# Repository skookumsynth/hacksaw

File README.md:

# hacksaw

The core to an expandable VCO. Based on the ubiquitous integrator-reset design seen a billion times.

Planned expanders:

* Variable sync
* Waveshaper (Ramp, Double ramp, Triangle, Sine, Pulse, "Even" (as seen on the Befaco Even and Bergfotron).
* Suboctave generator w/ -1 and -2 Saw waves
* "Supersaw" stack
* Some manner of wavefolder
* AM and FM

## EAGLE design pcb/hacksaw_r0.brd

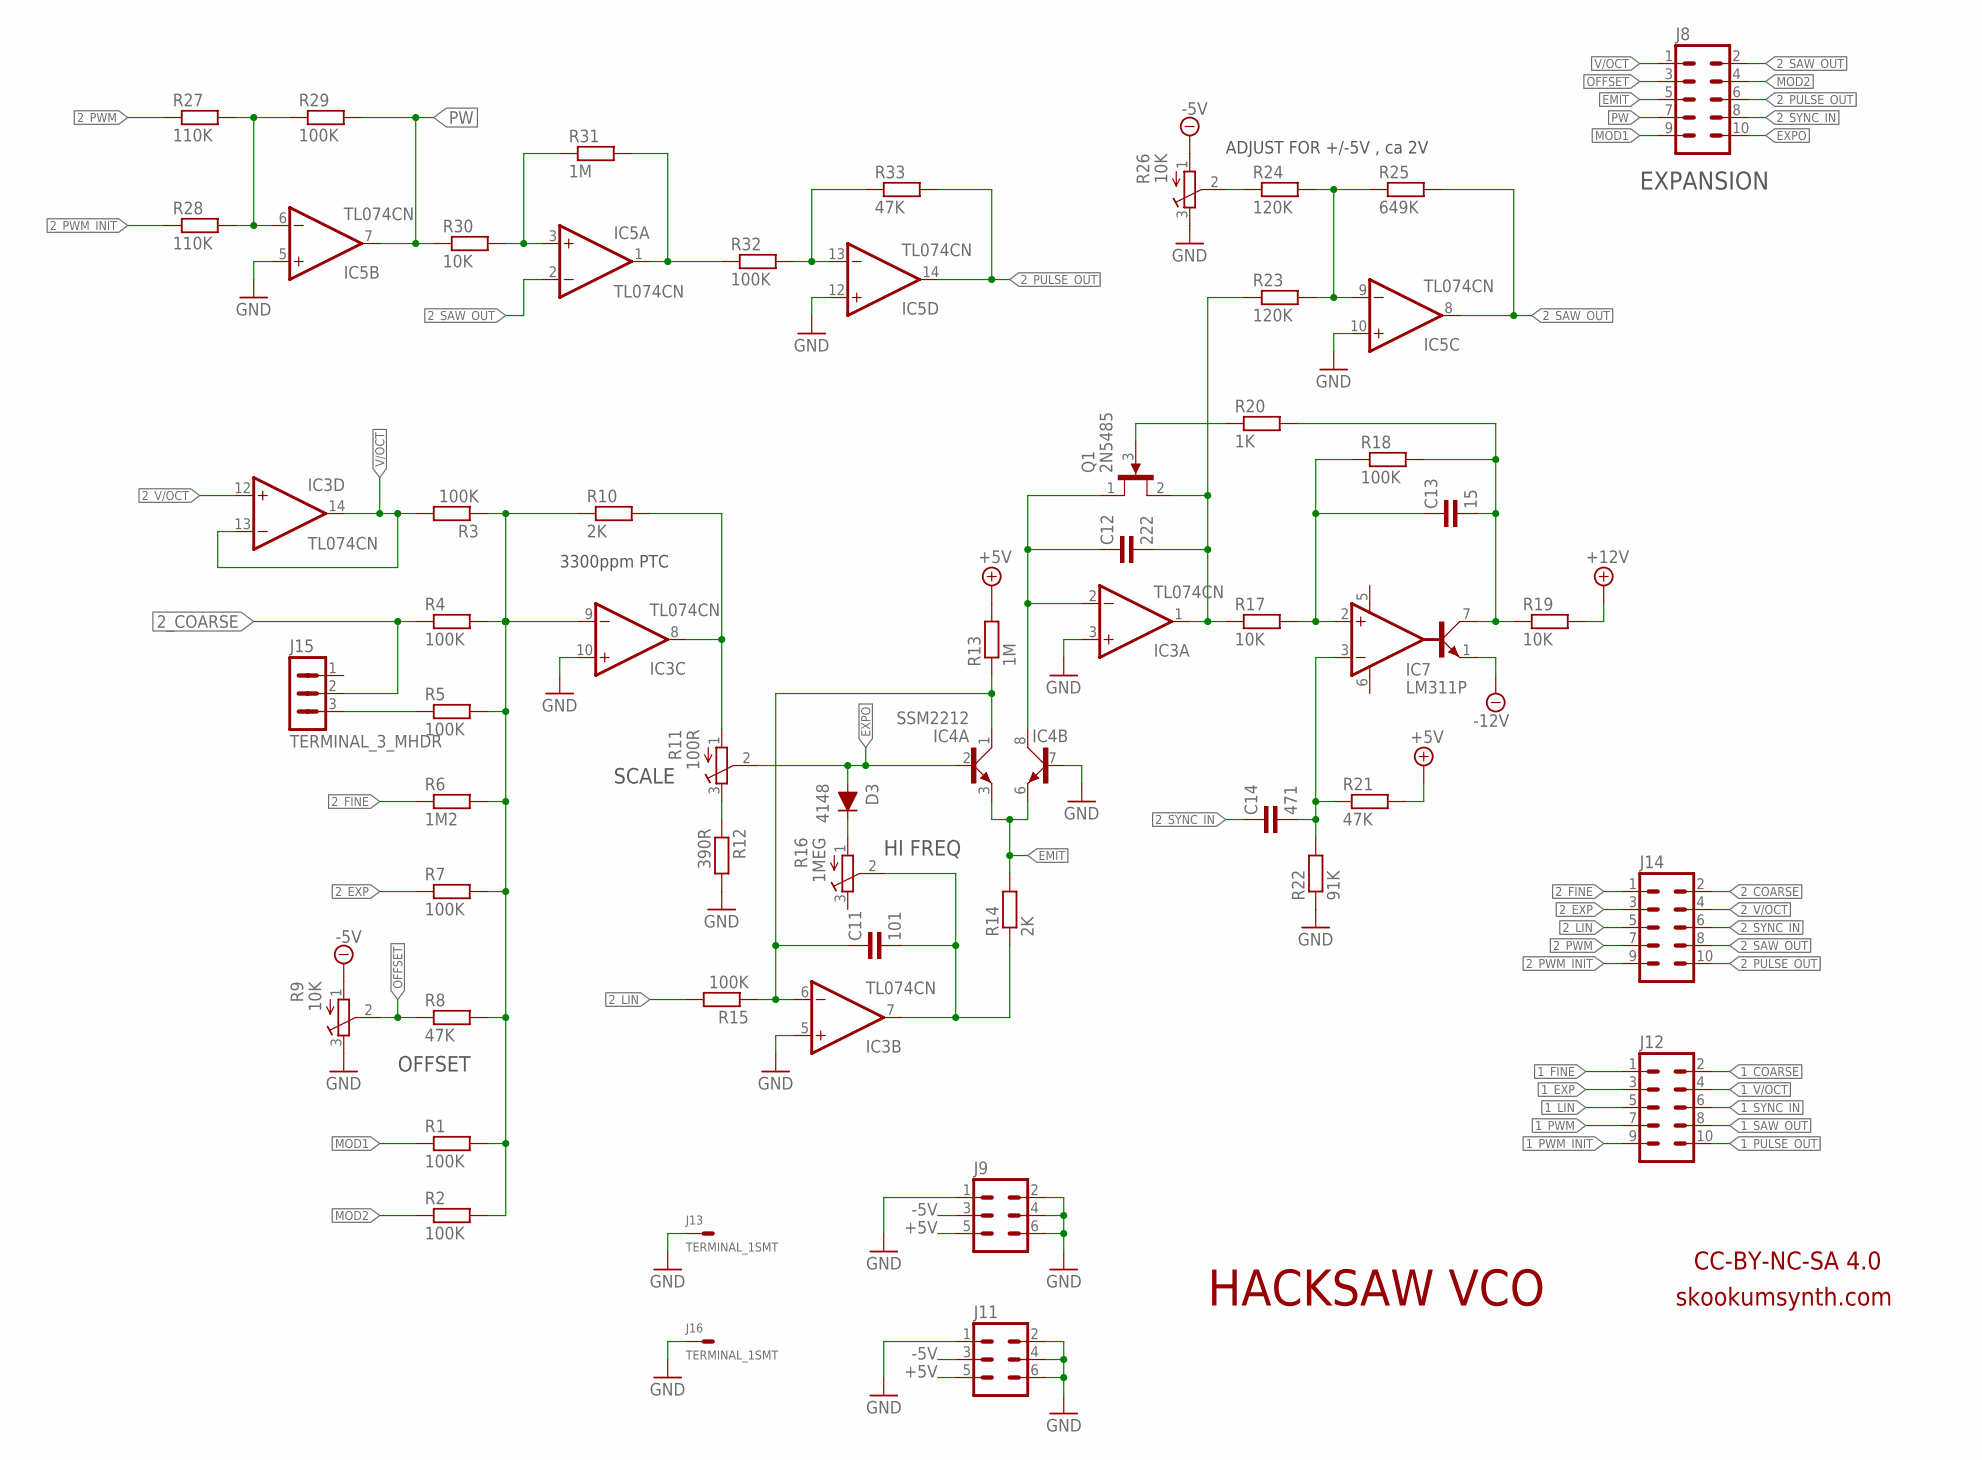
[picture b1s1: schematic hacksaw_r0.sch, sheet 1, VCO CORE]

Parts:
C11: 101; 0805
C12: 222; PHE450
C13: 15; 0805
C14: 471; 0805
D3: 4148; SOD123
IC3, IC5: TL074CN; DIL14
IC4: SSM2212; DIL8
IC7: LM311P; DIL8
J8, J14: CONN_HDR_5X21; HDR_M_5X2
J9: CONN_HDR_3X21; HDR_M_3X2
J11: CONN_HDR_3X22; HDR_M_3X2_REAR
J12: CONN_HDR_5X22; HDR_M_5X2_REAR
J13, J16: TERMINAL_1SMT; FP_GND
J15: TERMINAL_3_MHDR; HDR_M_3
Q1: 2N5485; TO-92_2
R1, R2, R3, R4, R5, R7, R15, R18, R29, R32: 100K; 0805
R6: 1M2; 0805
R8, R21, R33: 47K; 0805
R9, R26: 10K; PV36W
R10: 2K; RESISTOR_TH_1/4W
R11: 100R; PV36W
R12: 390R; 0805
R13, R31: 1M; 0805
R14: 2K; 0805
R16: 1MEG; PV36W
R17, R19, R30: 10K; 0805
R20: 1K; 0805
R22: 91K; 0805
R23, R24: 120K; 0805
R25: 649K; 0805
R27, R28: 110K; 0805

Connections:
1_COARSE: J12.2; also elsewhere on the board
1_EXP: J12.3; also elsewhere on the board
1_FINE: J12.1; also elsewhere on the board
1_LIN: J12.5; also elsewhere on the board
1_PULSE_OUT: J12.10; also elsewhere on the board
1_PWM: J12.7; also elsewhere on the board
1_PWM_INIT: J12.9; also elsewhere on the board
1_SAW_OUT: J12.8; also elsewhere on the board
1_SYNC_IN: J12.6; also elsewhere on the board
1_V/OCT: J12.4; also elsewhere on the board
2_COARSE: J14.2, J15.2, R4.1
2_EXP: J14.3, R7.1
2_FINE: J14.1, R6.1
2_LIN: J14.5, R15.2
2_PULSE_OUT: IC5.14 (OUT), J8.6, J14.10, R33.2
2_PWM: J14.7, R27.1
2_PWM_INIT: J14.9, R28.1
2_SAW_OUT: IC5.2 (-IN), IC5.8 (OUT), J8.2, J14.8, R25.2
2_SYNC_IN: C14.1 (+), J8.8, J14.6
2_SYNC_PULSE: C13.2 (-), IC7.7 (COL), R18.2, R19.1, R20.2
2_V/OCT: IC3.12 (+IN), J14.4
+5V: J9.5, J11.5, R13.2, R21.2; also elsewhere on the board
+12V: R19.2; also elsewhere on the board
-5V: J9.3, J11.3, R9.1, R26.1; also elsewhere on the board
-12V: IC7.1 (EMIT); also elsewhere on the board
C1: C11.1 (+), IC3.6 (-IN), IC4.1 (C), R13.1, R15.1
C2: C12.1 (+), IC3.2 (-IN), IC4.8 (C), Q1.1 (D)
CV: IC3.8 (OUT), R10.2, R11.1
EMIT: IC4.3 (E), IC4.6 (E), J8.5, R14.2
EXPO: D3.A, IC4.2 (B), J8.10, R11.2
GND: IC3.3 (+IN), IC3.5 (+IN), IC3.10 (+IN), IC4.7 (B), IC5.5 (+IN), IC5.10 (+IN), IC5.12 (+IN), J9.1, J9.2, J9.4, J9.6, J11.1, J11.2, J11.4, J11.6, J13.P$1, J16.P$1, R9.3, R12.2, R22.1, R26.3; also elsewhere on the board
MOD1: J8.9, R1.1
MOD2: J8.4, R2.1
unnamed: C13.1 (+), IC7.2 (+IN), R17.2, R18.1
unnamed: R11.3, R12.1
unnamed: IC5.1 (OUT), R31.2, R32.1
unnamed: D3.K (C), R16.1
unnamed: IC5.6 (-IN), R27.2, R28.2, R29.1
unnamed: Q1.3 (G), R20.1
unnamed: IC5.3 (+IN), R30.2, R31.1
unnamed: J15.3, R5.1
unnamed: IC5.13 (-IN), R32.2, R33.1
unnamed: IC3.9 (-IN), R1.2, R2.2, R3.1, R4.2, R5.2, R6.2, R7.2, R8.2, R10.1
unnamed: IC5.9 (-IN), R23.2, R24.2, R25.1
unnamed: R24.1, R26.2
unnamed: C11.2 (-), IC3.7 (OUT), R14.1, R16.2
OFFSET: J8.3, R8.1, R9.2
PW: IC5.7 (OUT), J8.7, R29.2, R30.1
RAW: C12.2 (-), IC3.1 (OUT), Q1.2 (S), R17.1, R23.1
RESET: C14.2 (-), IC7.3 (-IN), R21.1, R22.2
V/OCT: IC3.13 (-IN), IC3.14 (OUT), J8.1, R3.2

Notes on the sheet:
SCALE
3300ppm PTC
OFFSET
HI FREQ
ADJUST FOR +/-5V , ca 2V
EXPANSION
HACKSAW VCO
CC-BY-NC-SA 4.0
skookumsynth.com

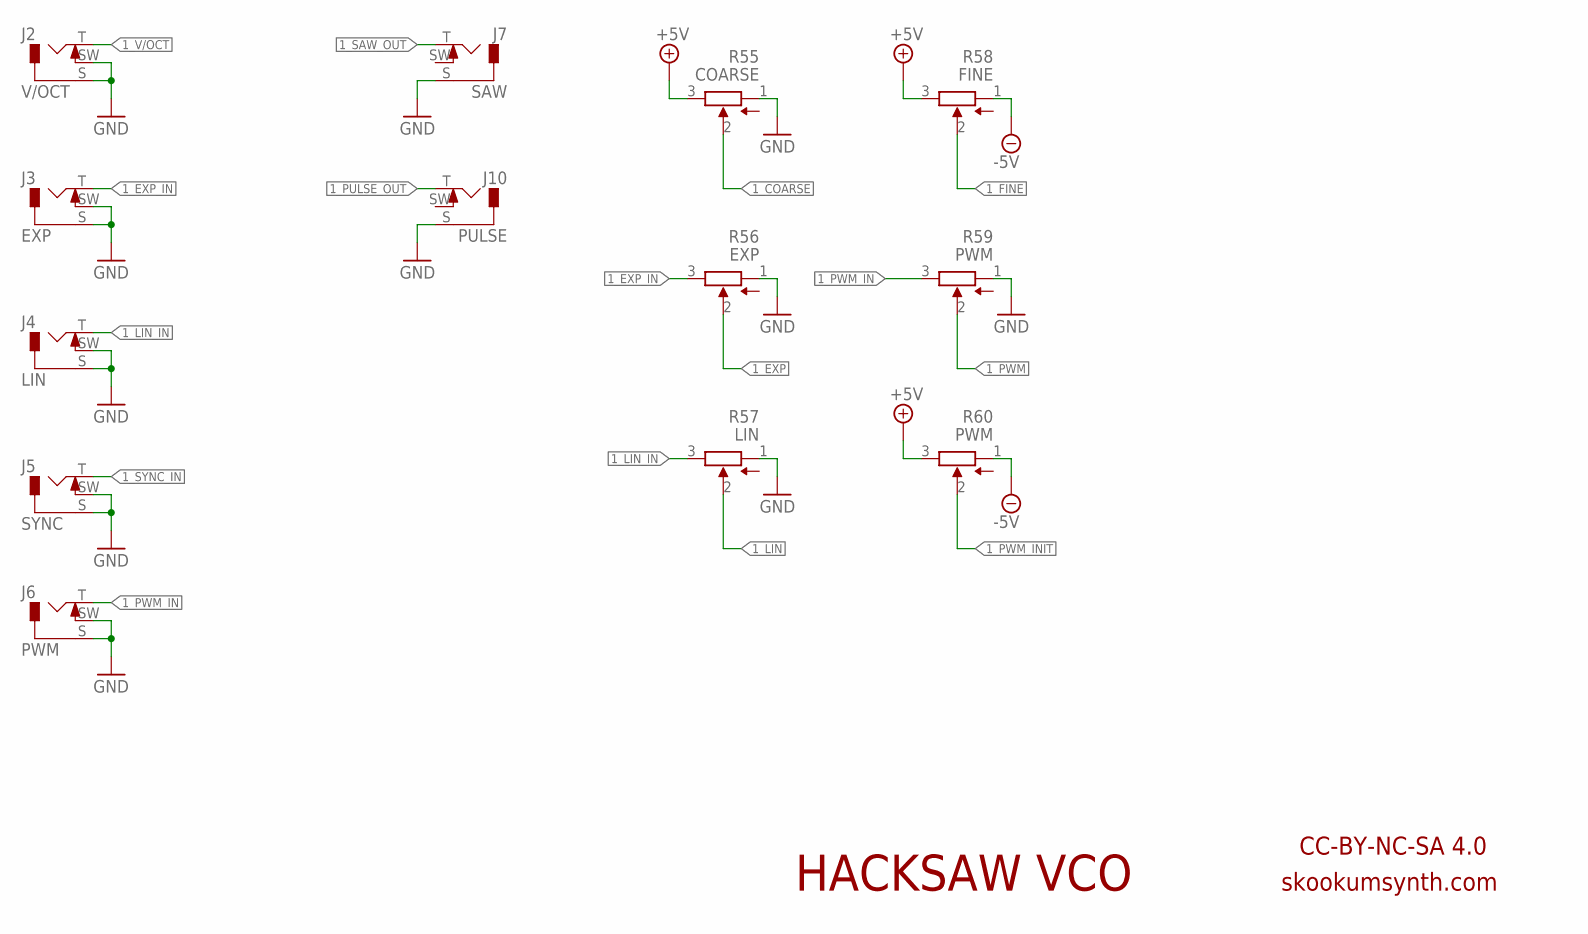
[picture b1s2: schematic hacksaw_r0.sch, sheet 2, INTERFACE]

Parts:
J2: V/OCT; WQP_PJ301M-12
J3: EXP; WQP_PJ301M-12
J4: LIN; WQP_PJ301M-12
J5: SYNC; WQP_PJ301M-12
J6: PWM; WQP_PJ301M-12
J7: SAW; WQP_PJ301M-12
J10: PULSE; WQP_PJ301M-12
R55: COARSE; PTV09
R56: EXP; PTV09
R57: LIN; PTV09
R58: FINE; PTV09
R59, R60: PWM; PTV09

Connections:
1_COARSE: R55.2; also elsewhere on the board
1_EXP: R56.2; also elsewhere on the board
1_EXP_IN: J3.T, R56.3
1_FINE: R58.2; also elsewhere on the board
1_LIN: R57.2; also elsewhere on the board
1_LIN_IN: J4.T, R57.3
1_PULSE_OUT: J10.T; also elsewhere on the board
1_PWM: R59.2; also elsewhere on the board
1_PWM_IN: J6.T, R59.3
1_PWM_INIT: R60.2; also elsewhere on the board
1_SAW_OUT: J7.T; also elsewhere on the board
1_SYNC_IN: J5.T; also elsewhere on the board
1_V/OCT: J2.T; also elsewhere on the board
+5V: R55.3, R58.3, R60.3; also elsewhere on the board
-5V: R58.1, R60.1; also elsewhere on the board
GND: J2.S, J2.SW, J3.S, J3.SW, J4.S, J4.SW, J5.S, J5.SW, J6.S, J6.SW, J7.S, J10.S, R55.1, R56.1, R57.1, R59.1; also elsewhere on the board

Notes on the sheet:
HACKSAW VCO
CC-BY-NC-SA 4.0
skookumsynth.com

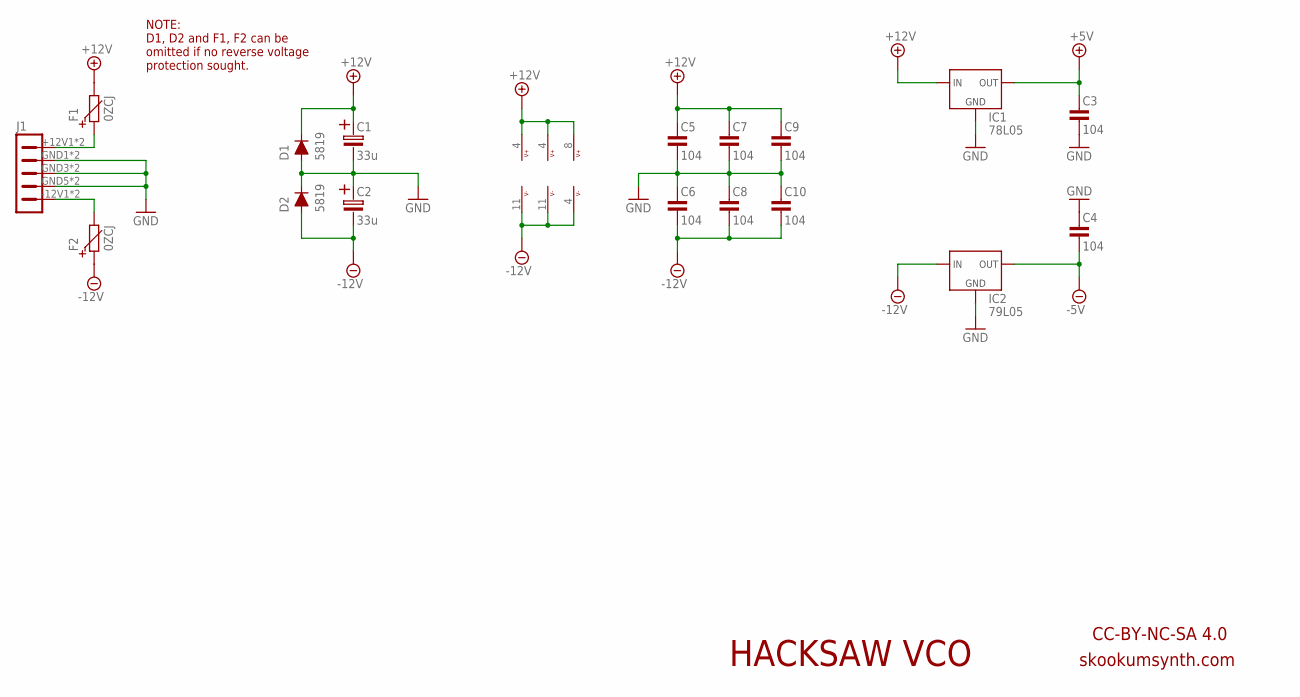
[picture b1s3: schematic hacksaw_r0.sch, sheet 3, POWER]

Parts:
C1, C2: 33u; CAP_POL_2.5-6
C3, C4, C5, C6, C7, C8, C9, C10: 104; 0805
D1, D2: 5819; SOD123
F1, F2: 0ZCJ; 1206
IC1: 78L05; TO-92_2
IC2: 79L05; TO-92_2
IC3, IC5: TL074CN; DIL14
IC7: LM311P; DIL8
J1: HDR_POWER_10_VERT; HDR_POWER_10

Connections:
+5V: C3.1 (+), IC1.1 (OUT); also elsewhere on the board
+12V: C1.+, C5.1 (+), C7.1 (+), C9.1 (+), D1.K (C), F1.2, IC1.3 (IN), IC3.4 (V+), IC5.4 (V+), IC7.8 (V+); also elsewhere on the board
-5V: C4.2 (-), IC2.3 (OUT); also elsewhere on the board
-12V: C2.-, C6.2 (-), C8.2 (-), C10.2 (-), D2.A, F2.1, IC2.2 (IN), IC3.11 (V-), IC5.11 (V-), IC7.4 (V-); also elsewhere on the board
GND: C1.-, C2.+, C3.2 (-), C4.1 (+), C5.2 (-), C6.1 (+), C7.2 (-), C8.1 (+), C9.2 (-), C10.1 (+), D1.A, D2.K (C), IC1.2 (GND), IC2.1 (GND), J1.GND1 (2), J1.GND2 (2), J1.GND3 (3), J1.GND4 (3), J1.GND5 (4), J1.GND6 (4); also elsewhere on the board
unnamed: F1.1, J1.+12V1 (1), J1.+12V2 (1)
unnamed: F2.2, J1.-12V1 (5), J1.-12V2 (5)

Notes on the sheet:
HACKSAW VCO
CC-BY-NC-SA 4.0
skookumsynth.com
NOTE: D1, D2 and F1, F2 can be omitted if no reverse voltage protection sought.

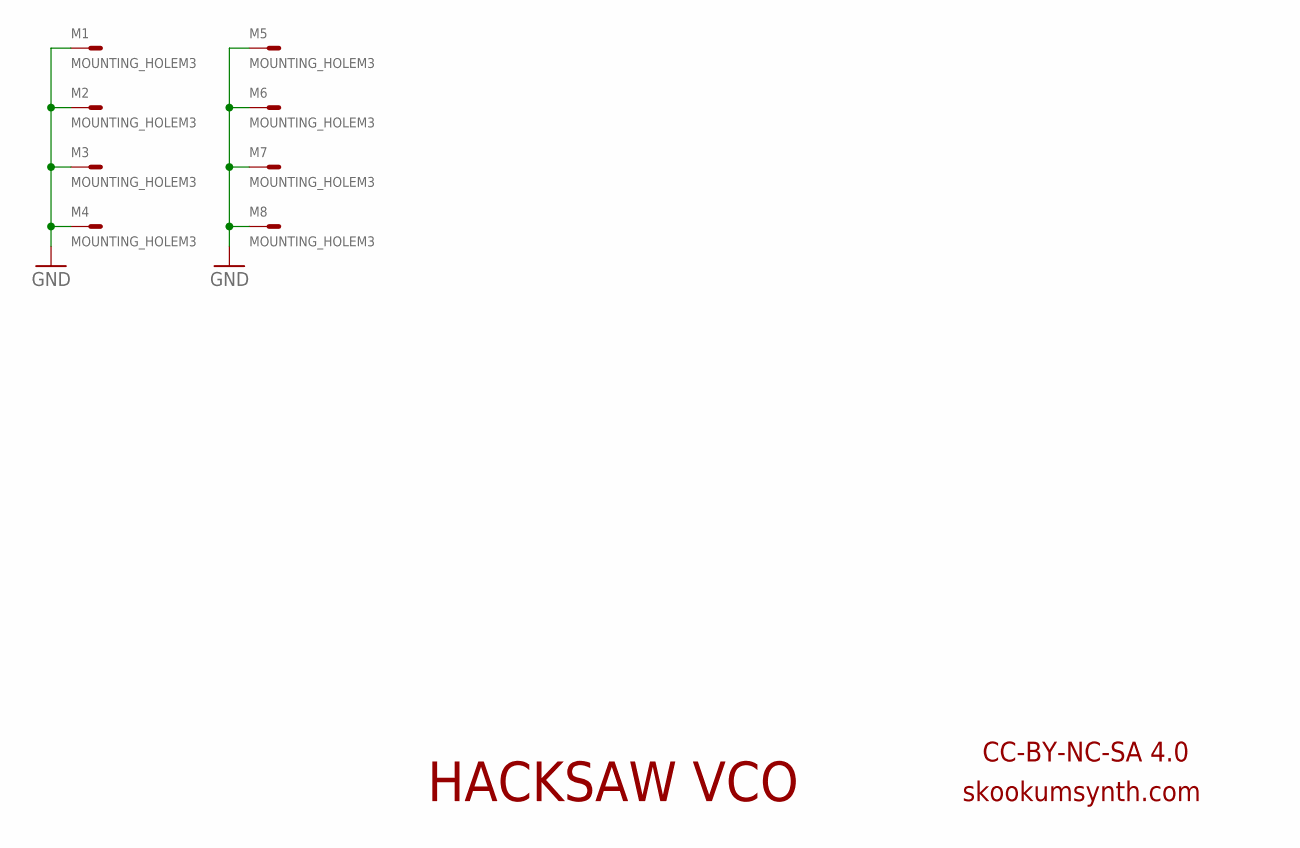
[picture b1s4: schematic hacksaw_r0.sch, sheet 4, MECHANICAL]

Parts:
M1, M2, M3, M4, M5, M6, M7, M8: MOUNTING_HOLEM3; M3

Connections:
GND: M1.M3, M2.M3, M3.M3, M4.M3, M5.M3, M6.M3, M7.M3, M8.M3; also elsewhere on the board

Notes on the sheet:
HACKSAW VCO
CC-BY-NC-SA 4.0
skookumsynth.com

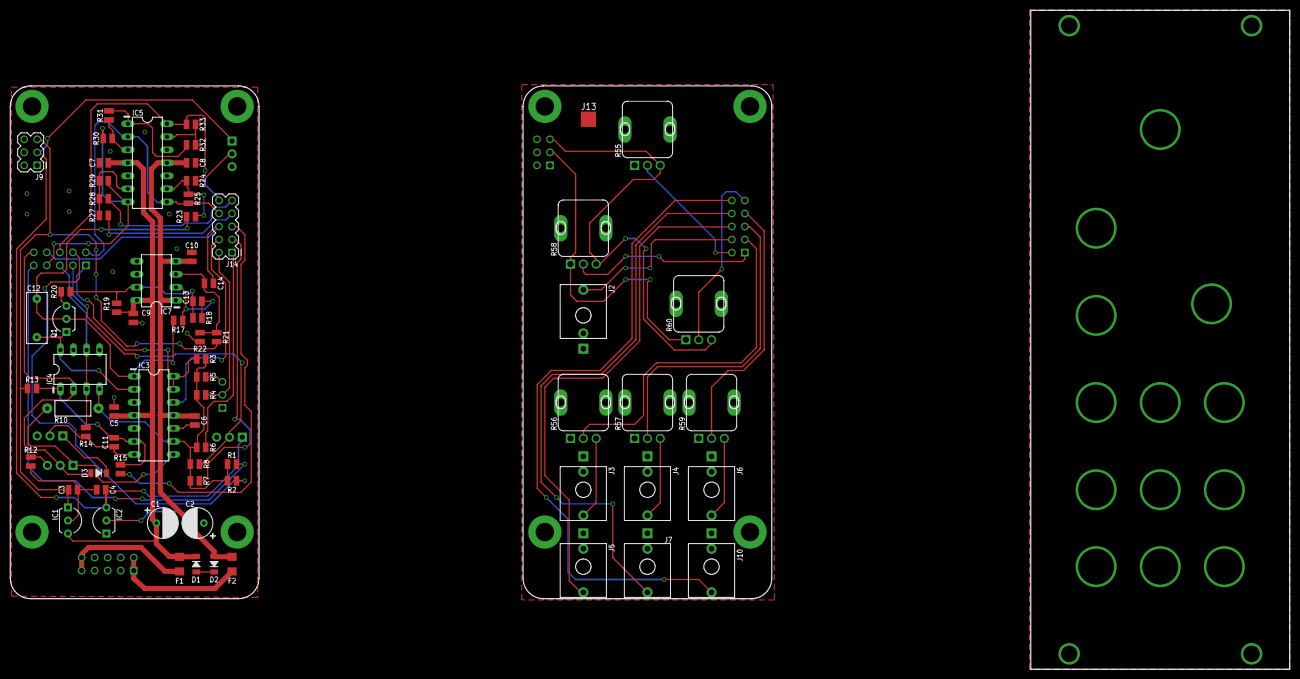
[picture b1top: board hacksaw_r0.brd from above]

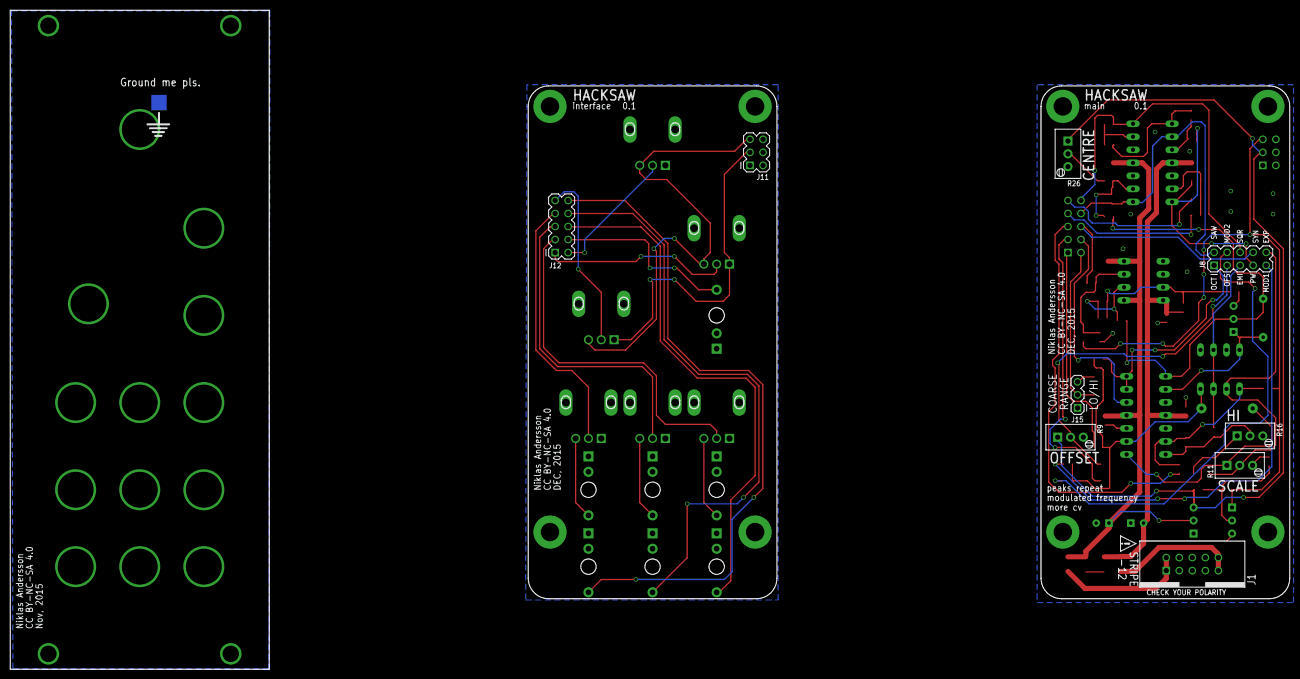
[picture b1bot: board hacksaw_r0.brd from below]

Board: 2 copper layers, 249.5 x 128.5 mm, 91 parts (10 on the bottom side), 56 nets.

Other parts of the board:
E$1, E$2: PANEL_OUTPUT
